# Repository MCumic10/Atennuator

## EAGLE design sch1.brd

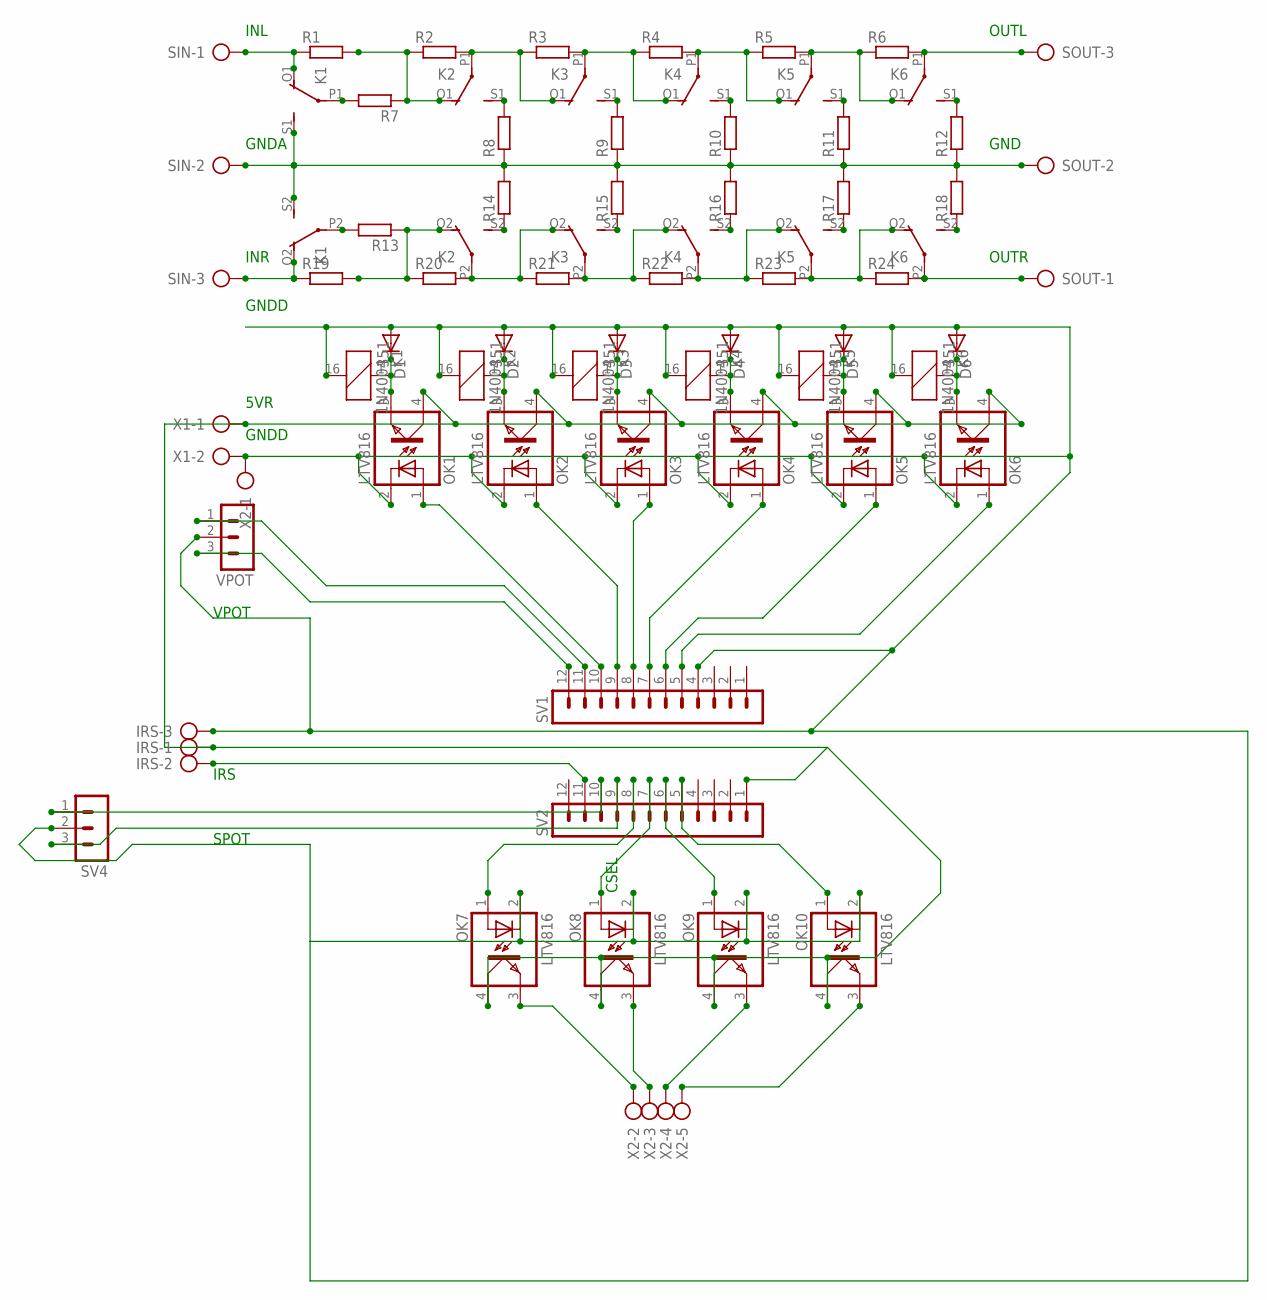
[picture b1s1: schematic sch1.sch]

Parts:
D1, D2, D3, D4, D5, D6: 1N4004; DO41-10
IRS: AK500/3
K1, K2, K3, K4, K5, K6: 351
OK1, OK2, OK3, OK4, OK5, OK6, OK7, OK8, OK9, OK10: LTV816; DIL04
R1, R2, R3, R4, R5, R6, R7, R8, R9, R10, R11, R12, R13, R14, R15, R16, R17, R18, R19, R20, R21, R22, R23, R24: R-EU_0204/7; 0204/7
SIN: AK500/3
SOUT: AK500/3
SV1, SV2: MA12-1
SV4: MA03-1
VPOT: MA03-1
X1: AK500/2
X2: AK500/5

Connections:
GNDA: K1.S1 (S), K1.S2 (S), R8.1, R9.1, R10.1, R11.1, R12.1, R14.2, R15.2, R16.2, R17.2, R18.2, SIN.2, SOUT.2
GNDD: D1.A, D2.A, D3.A, D4.A, D5.A, D6.A, IRS.3, K1.16 (2), K2.16 (2), K3.16 (2), K4.16 (2), K5.16 (2), K6.16 (2), OK1.2 (C), OK2.2 (C), OK3.2 (C), OK4.2 (C), OK5.2 (C), OK6.2 (C), OK7.2 (C), OK8.2 (C), OK9.2 (C), OK10.2 (C), SV1.4, SV4.2, VPOT.2, X1.2, X2.1
unnamed: K2.O1 (O), R1.2, R2.1, R7.1
unnamed: K2.P1, K3.O1 (O), R2.2, R3.1
unnamed: K3.P1, K4.O1 (O), R3.2, R4.1
unnamed: K4.P1, K5.O1 (O), R4.2, R5.1
unnamed: K5.P1, K6.O1 (O), R5.2, R6.1
unnamed: K6.P1, R6.2, SOUT.3
unnamed: K1.O1 (O), R1.1, SIN.1
unnamed: K1.P2, R13.2
unnamed: K2.S1 (S), R8.2
unnamed: K3.S1 (S), R9.2
unnamed: K4.S1 (S), R10.2
unnamed: K5.S1 (S), R11.2
unnamed: K6.S1 (S), R12.2
unnamed: K1.P1, R7.2
unnamed: K1.O2 (O), R19.1, SIN.3
unnamed: K5.S2 (S), R17.1
unnamed: K4.S2 (S), R16.1
unnamed: K3.S2 (S), R15.1
unnamed: K2.S2 (S), R14.1
unnamed: K6.S2 (S), R18.1
unnamed: OK7.1 (A), SV2.8
unnamed: SV1.12, VPOT.3
unnamed: D1.C, K1.1, OK1.3 (EMIT)
unnamed: D2.C, K2.1, OK2.3 (EMIT)
unnamed: D3.C, K3.1, OK3.3 (EMIT)
unnamed: D4.C, K4.1, OK4.3 (EMIT)
unnamed: D5.C, K5.1, OK5.3 (EMIT)
unnamed: K2.P2, K3.O2 (O), R20.2, R21.1
unnamed: K3.P2, K4.O2 (O), R21.2, R22.1
unnamed: K4.P2, K5.O2 (O), R22.2, R23.1
unnamed: K2.O2 (O), R13.1, R19.2, R20.1
unnamed: K6.P2, R24.2, SOUT.1
unnamed: D6.C, K6.1, OK6.3 (EMIT)
unnamed: K5.P2, K6.O2 (O), R23.2, R24.1
unnamed: SV1.11, VPOT.1
unnamed: OK6.1 (A), SV1.5
unnamed: OK5.1 (A), SV1.6
unnamed: OK4.1 (A), SV1.7
unnamed: OK3.1 (A), SV1.8
unnamed: OK2.1 (A), SV1.9
unnamed: OK1.1 (A), SV1.10
unnamed: SV2.10, SV4.1
unnamed: SV2.9, SV4.3
unnamed: OK8.1 (A), SV2.7
unnamed: OK9.1 (A), SV2.6
unnamed: OK10.1 (A), SV2.5
unnamed: IRS.2, SV2.11
unnamed: IRS.1, OK1.4 (COL), OK2.4 (COL), OK3.4 (COL), OK4.4 (COL), OK5.4 (COL), OK6.4 (COL), OK7.4 (COL), OK8.4 (COL), OK9.4 (COL), OK10.4 (COL), SV2.1, X1.1
unnamed: OK7.3 (EMIT), X2.2
unnamed: OK8.3 (EMIT), X2.3
unnamed: OK9.3 (EMIT), X2.4
unnamed: OK10.3 (EMIT), X2.5

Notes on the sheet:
INL
INR
GNDA
OUTL
OUTR
GND
GNDD
5VR
VPOT
IRS
CSEL
SPOT

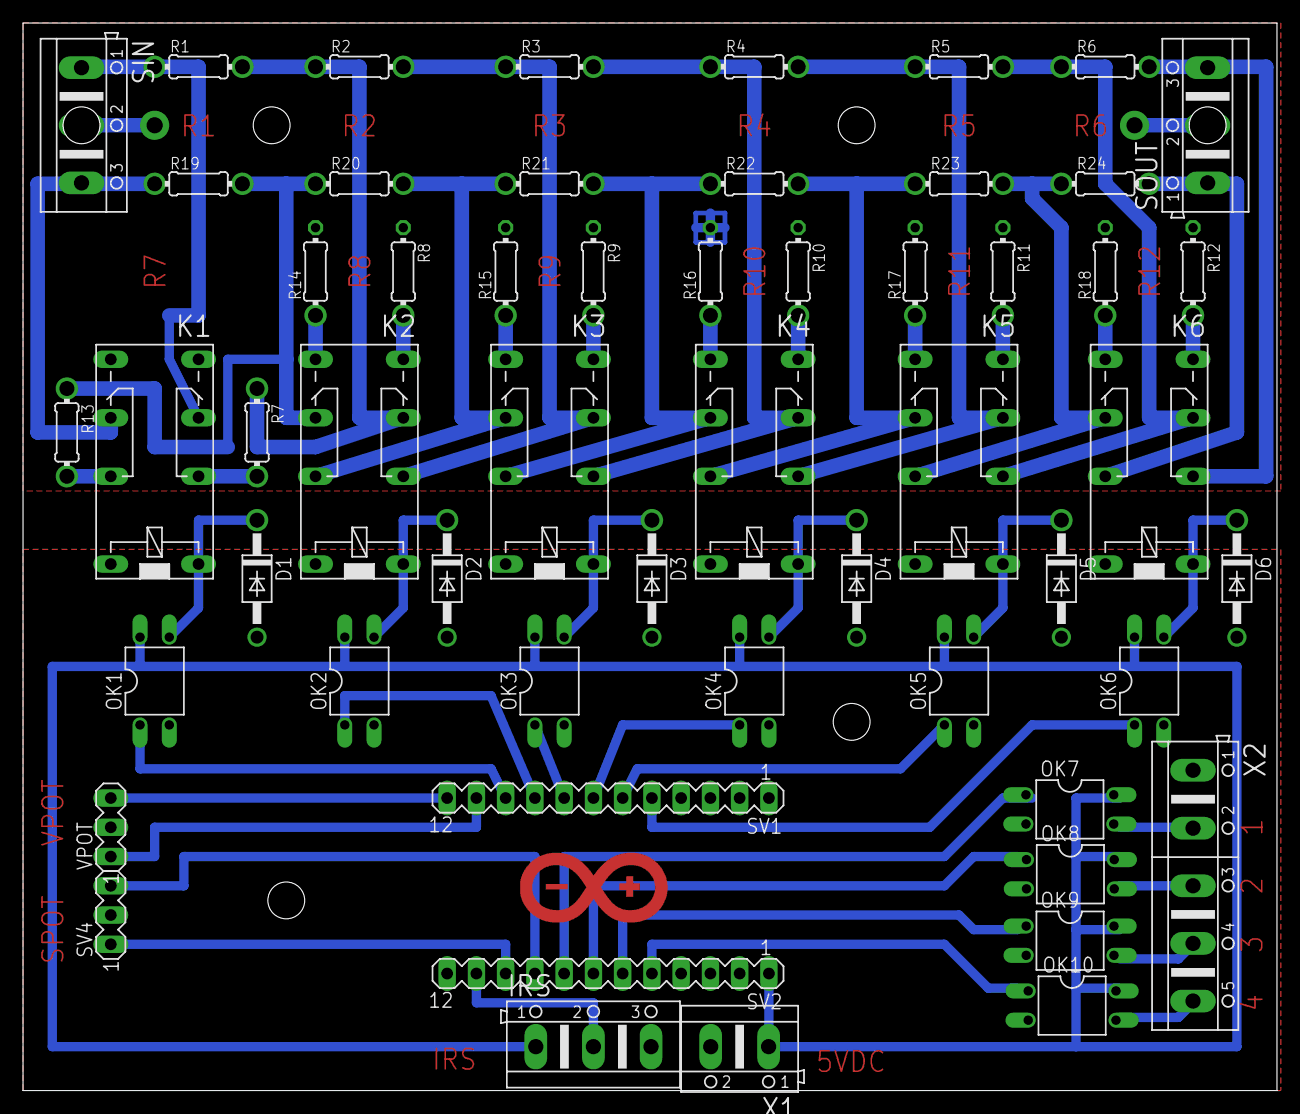
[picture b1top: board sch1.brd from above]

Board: 2 copper layers, 108.9 x 92.7 mm, 55 parts (0 on the bottom side), 54 nets.

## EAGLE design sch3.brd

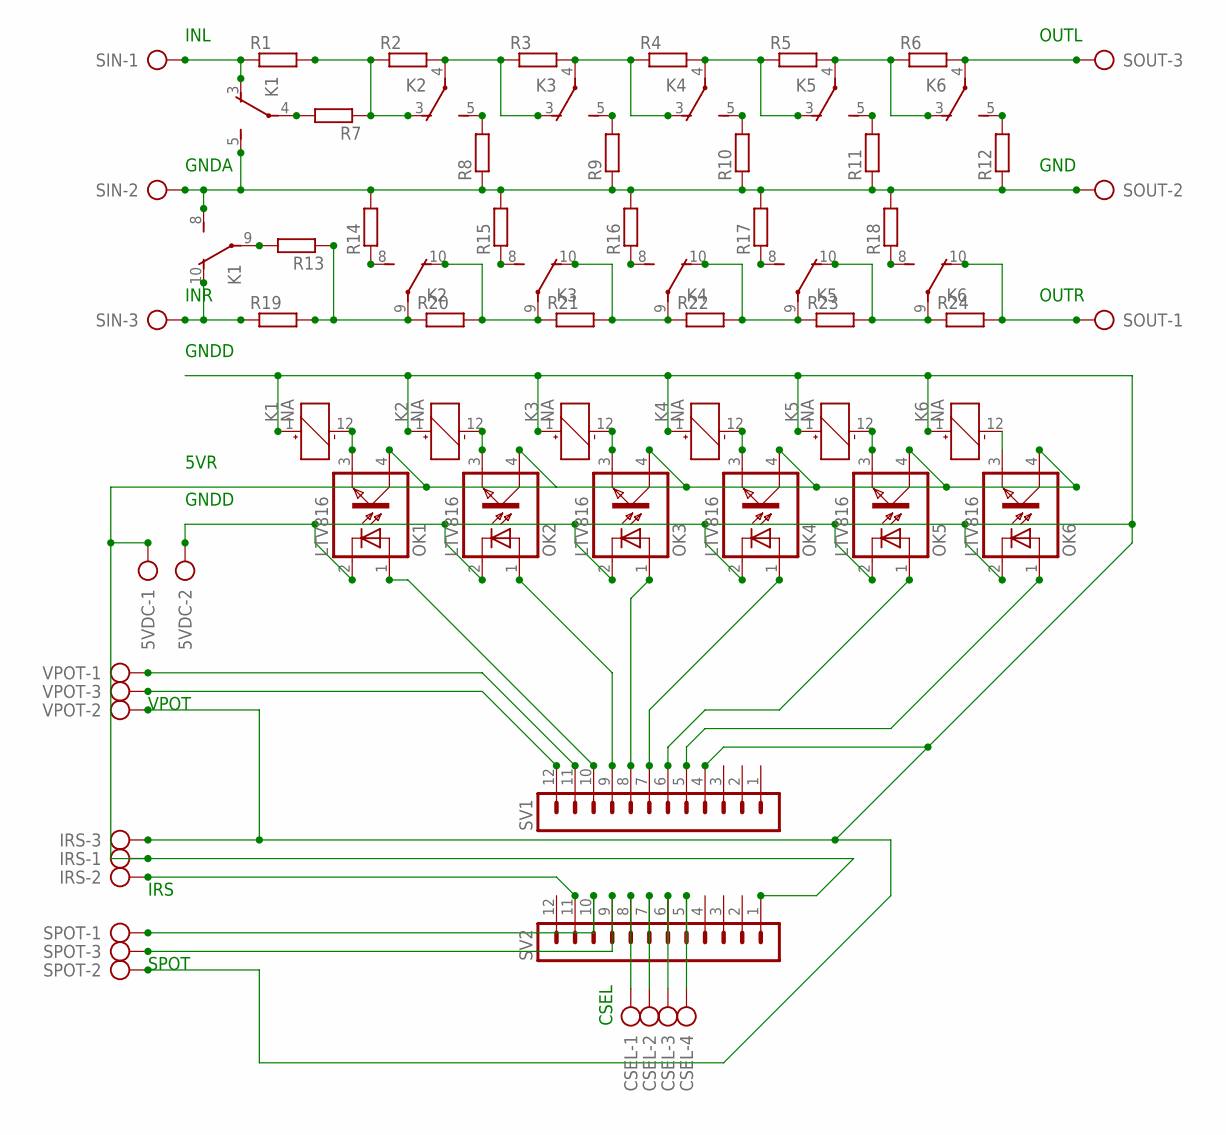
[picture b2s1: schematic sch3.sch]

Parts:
5VDC: AK500/2
CSEL: AK500/4
IRS: AK500/3
K1, K2, K3, K4, K5, K6: NA
OK1, OK2, OK3, OK4, OK5, OK6: LTV816; DIL04
R1, R2, R3, R4, R5, R6, R7, R8, R9, R10, R11, R12, R13, R14, R15, R16, R17, R18, R19, R20, R21, R22, R23, R24: R-EU_0204/7; 0204/7
SIN: AK500/3
SOUT: AK500/3
SPOT: AK500/3
SV1, SV2: MA12-1
VPOT: AK500/3

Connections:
GNDA: K1.5 (S), K1.8 (S), R8.1, R9.1, R10.1, R11.1, R12.1, R14.2, R15.2, R16.2, R17.2, R18.2, SIN.2, SOUT.2
GNDD: 5VDC.2, IRS.3, K1.1 (+), K2.1 (+), K3.1 (+), K4.1 (+), K5.1 (+), K6.1 (+), OK1.2 (C), OK2.2 (C), OK3.2 (C), OK4.2 (C), OK5.2 (C), OK6.2 (C), SPOT.2, SV1.4, VPOT.2
unnamed: K2.3 (O), R1.2, R2.1, R7.1
unnamed: K2.4, K3.3 (O), R2.2, R3.1
unnamed: K3.4, K4.3 (O), R3.2, R4.1
unnamed: K4.4, K5.3 (O), R4.2, R5.1
unnamed: K5.4, K6.3 (O), R5.2, R6.1
unnamed: K6.4, R6.2, SOUT.3
unnamed: K1.3 (O), R1.1, SIN.1
unnamed: K1.9, R13.2
unnamed: K2.5 (S), R8.2
unnamed: K3.5 (S), R9.2
unnamed: K4.5 (S), R10.2
unnamed: K5.5 (S), R11.2
unnamed: K6.5 (S), R12.2
unnamed: K1.4, R7.2
unnamed: K1.10 (O), R19.1, SIN.3
unnamed: K2.8 (S), R14.1
unnamed: K3.8 (S), R15.1
unnamed: K4.8 (S), R16.1
unnamed: K5.8 (S), R17.1
unnamed: K6.8 (S), R18.1
unnamed: SV1.11, VPOT.1
unnamed: SV1.12, VPOT.3
unnamed: K1.12 (-), OK1.3 (EMIT)
unnamed: K2.12 (-), OK2.3 (EMIT)
unnamed: K3.12 (-), OK3.3 (EMIT)
unnamed: K4.12 (-), OK4.3 (EMIT)
unnamed: K2.9, R13.1, R19.2, R20.1
unnamed: K2.10 (O), K3.9, R20.2, R21.1
unnamed: K3.10 (O), K4.9, R21.2, R22.1
unnamed: K4.10 (O), K5.9, R22.2, R23.1
unnamed: K5.10 (O), K6.9, R23.2, R24.1
unnamed: K6.10 (O), R24.2, SOUT.1
unnamed: K5.12 (-), OK5.3 (EMIT)
unnamed: K6.12 (-), OK6.3 (EMIT)
unnamed: OK6.1 (A), SV1.5
unnamed: OK5.1 (A), SV1.6
unnamed: OK4.1 (A), SV1.7
unnamed: OK3.1 (A), SV1.8
unnamed: OK2.1 (A), SV1.9
unnamed: OK1.1 (A), SV1.10
unnamed: IRS.2, SV2.11
unnamed: CSEL.1, SV2.8
unnamed: CSEL.2, SV2.7
unnamed: CSEL.3, SV2.6
unnamed: CSEL.4, SV2.5
unnamed: SPOT.1, SV2.10
unnamed: SPOT.3, SV2.9
unnamed: 5VDC.1, IRS.1, OK1.4 (COL), OK2.4 (COL), OK3.4 (COL), OK4.4 (COL), OK5.4 (COL), OK6.4 (COL), SV2.1

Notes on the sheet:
INL
INR
GNDA
OUTL
OUTR
GND
GNDD
5VR
VPOT
IRS
CSEL
SPOT

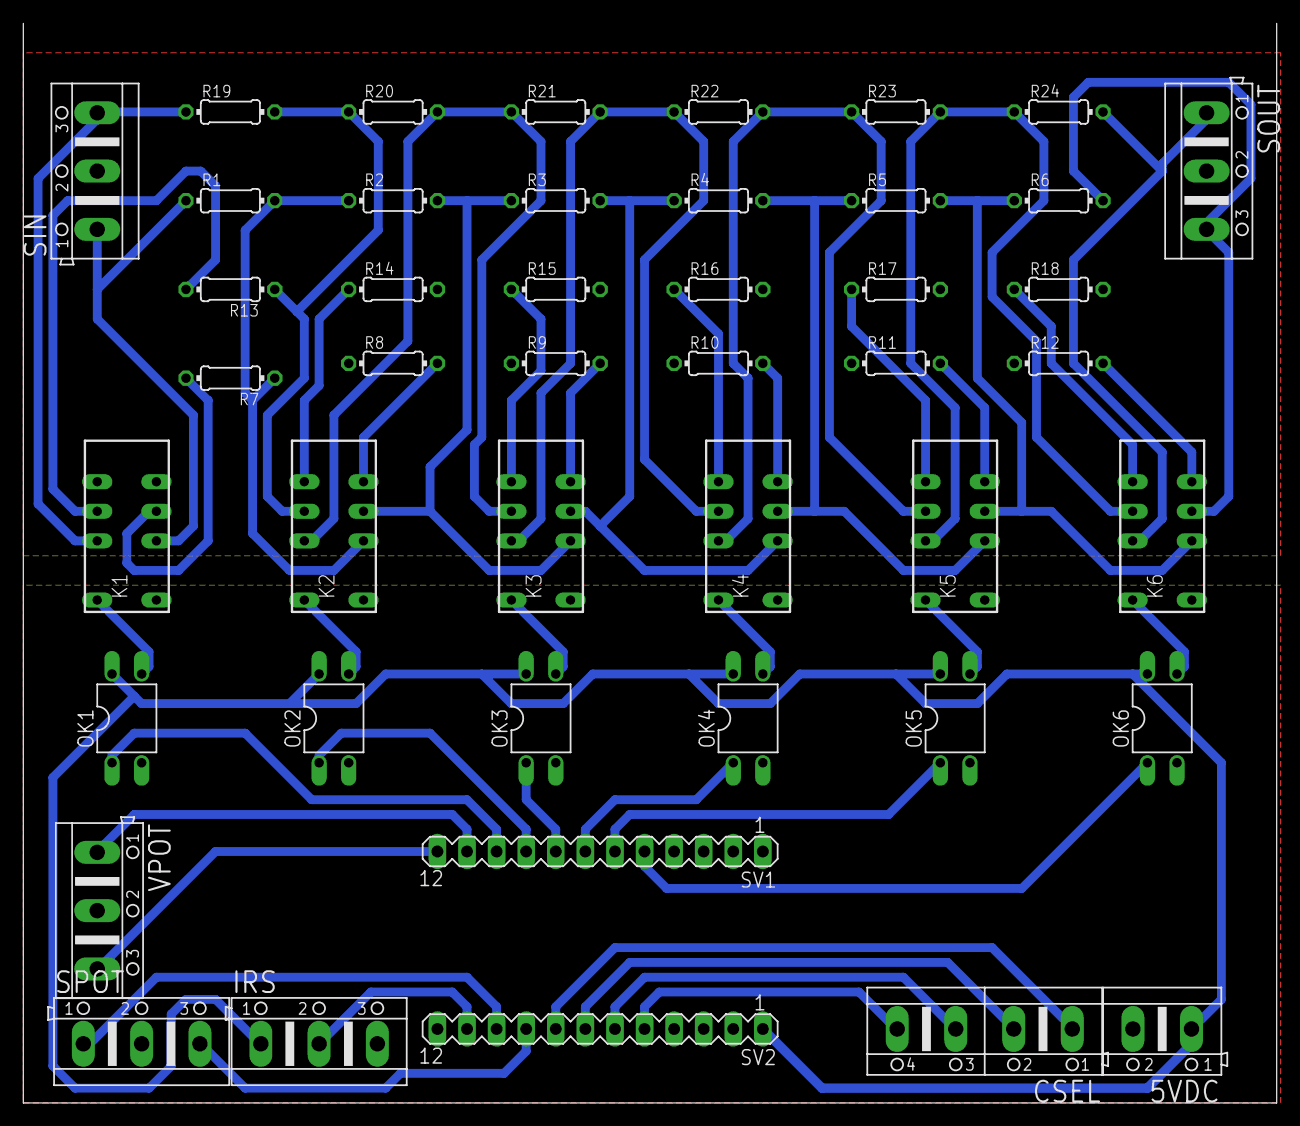
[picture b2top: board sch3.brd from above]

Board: 2 copper layers, 107.6 x 92.7 mm, 45 parts (0 on the bottom side), 50 nets.

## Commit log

2016-04-28 :octocat: Added .gitattributes & .gitignore files
2016-04-28 Added gainclone to scheme
    Need to add control for mute relay
2016-04-28 Remove junk
2016-05-04 added ground fill on bottom
